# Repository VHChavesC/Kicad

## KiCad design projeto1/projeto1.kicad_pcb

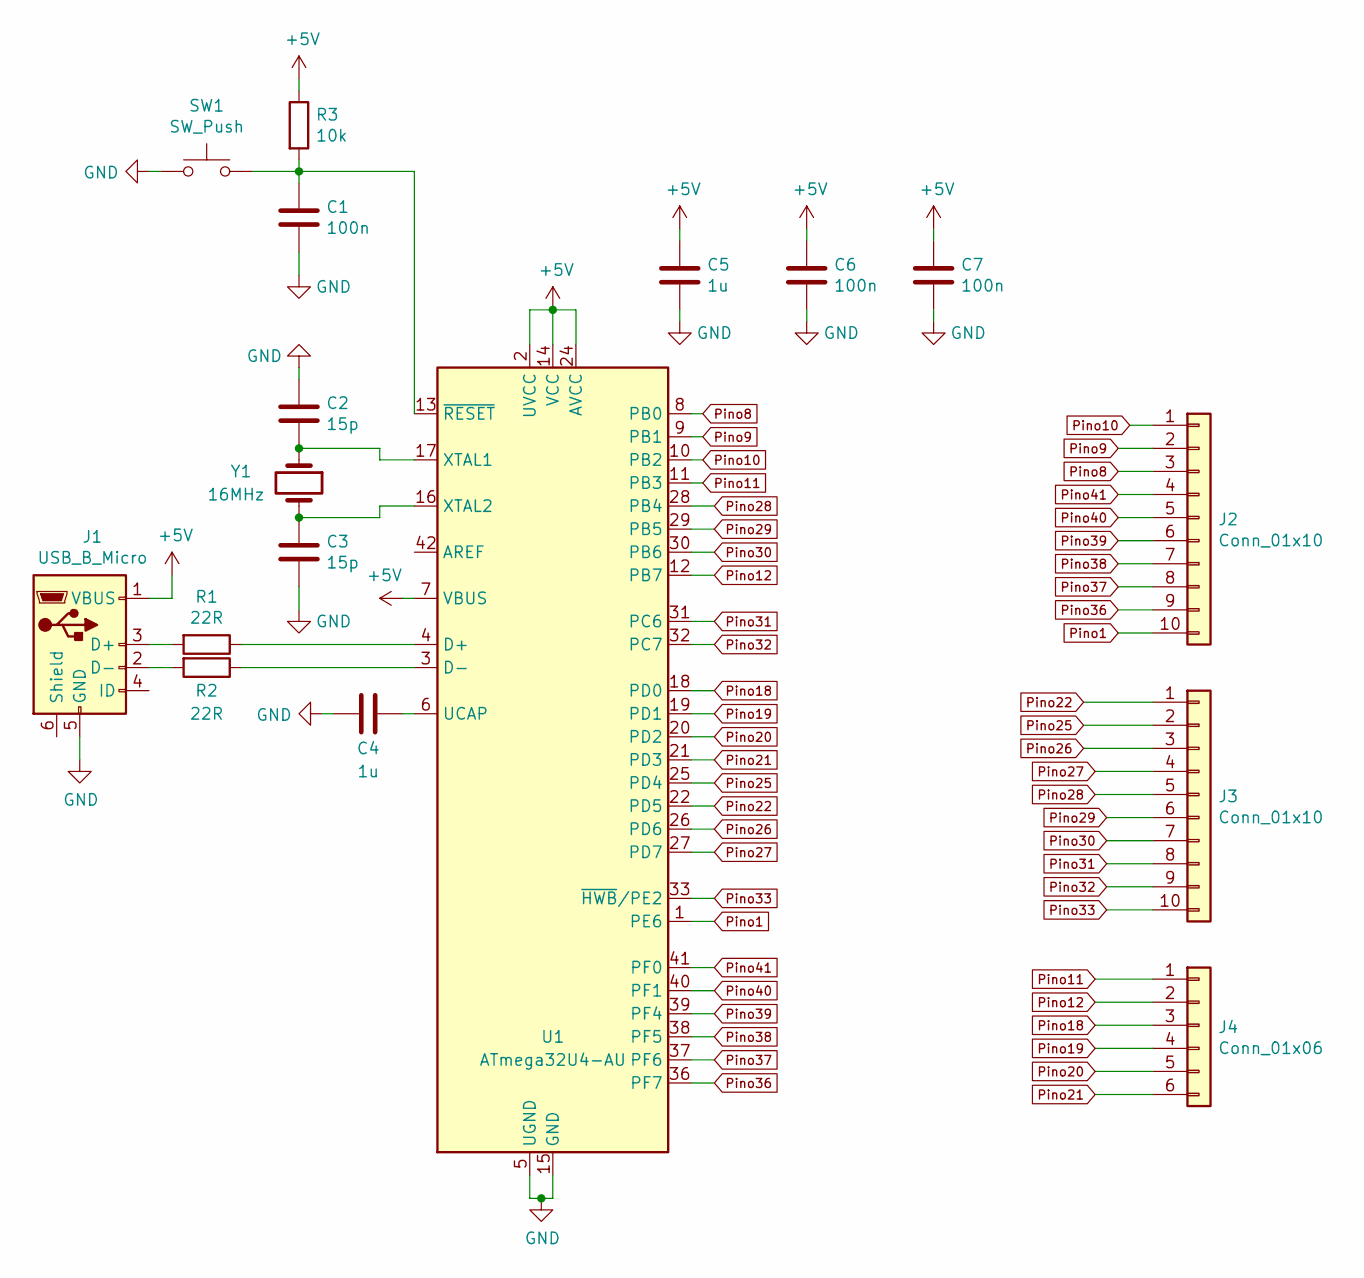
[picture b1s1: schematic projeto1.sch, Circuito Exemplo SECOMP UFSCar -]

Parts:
C1, C6, C7: 100n; C_0805_2012Metric_Pad1.15x1.40mm_HandSolder
C2, C3: 15p; C_0805_2012Metric_Pad1.15x1.40mm_HandSolder
C4, C5: 1u; C_0805_2012Metric_Pad1.15x1.40mm_HandSolder
J1: USB_B_Micro; USB_Mini-B_AdamTech_MUSB-B5-S-VT-TSMT-1_SMD_Vertical
J2, J3: Conn_01x10; PinHeader_1x10_P2.54mm_Vertical
J4: Conn_01x06; PinHeader_1x06_P2.54mm_Vertical
R1, R2: 22R; R_1206_3216Metric_Pad1.42x1.75mm_HandSolder
R3: 10k; R_1206_3216Metric_Pad1.42x1.75mm_HandSolder
SW1: SW_Push; SW_PUSH_6mm
U1: ATmega32U4-AU; TQFP-44_10x10mm_P0.8mm
Y1: 16MHz; Crystal_SMD_5032-2Pin_5.0x3.2mm_HandSoldering

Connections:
+5V: C5.1, C6.1, C7.1, J1.1 (VBUS), R3.1, U1.2 (UVCC), U1.7 (VBUS), U1.14 (VCC), U1.24 (AVCC), U1.34 (VCC), U1.44 (AVCC)
GND: C1.2, C2.1, C3.2, C4.2, C5.2, C6.2, C7.2, J1.5 (GND), SW1.1, U1.5 (UGND), U1.15 (GND), U1.23 (GND), U1.35 (GND), U1.43 (GND)
unnamed: C1.1, R3.2, SW1.2, U1.13 (~RESET)
unnamed: C2.2, U1.17 (XTAL1), Y1.1
unnamed: C3.1, U1.16 (XTAL2), Y1.2
unnamed: C4.1, U1.6 (UCAP)
unnamed: J1.2 (D-), R2.2
unnamed: J1.3 (D+), R1.2
unnamed: R1.1, U1.4 (D+)
unnamed: R2.1, U1.3 (D-)
Pino1: J2.10, U1.1 (PE6)
Pino8: J2.3, U1.8 (PB0)
Pino9: J2.2, U1.9 (PB1)
Pino10: J2.1, U1.10 (PB2)
Pino11: J4.1, U1.11 (PB3)
Pino12: J4.2, U1.12 (PB7)
Pino18: J4.3, U1.18 (PD0)
Pino19: J4.4, U1.19 (PD1)
Pino20: J4.5, U1.20 (PD2)
Pino21: J4.6, U1.21 (PD3)
Pino22: J3.1, U1.22 (PD5)
Pino25: J3.2, U1.25 (PD4)
Pino26: J3.3, U1.26 (PD6)
Pino27: J3.4, U1.27 (PD7)
Pino28: J3.5, U1.28 (PB4)
Pino29: J3.6, U1.29 (PB5)
Pino30: J3.7, U1.30 (PB6)
Pino31: J3.8, U1.31 (PC6)
Pino32: J3.9, U1.32 (PC7)
Pino33: J3.10, U1.33 (~HWB~/PE2)
Pino36: J2.9, U1.36 (PF7)
Pino37: J2.8, U1.37 (PF6)
Pino38: J2.7, U1.38 (PF5)
Pino39: J2.6, U1.39 (PF4)
Pino40: J2.5, U1.40 (PF1)
Pino41: J2.4, U1.41 (PF0)

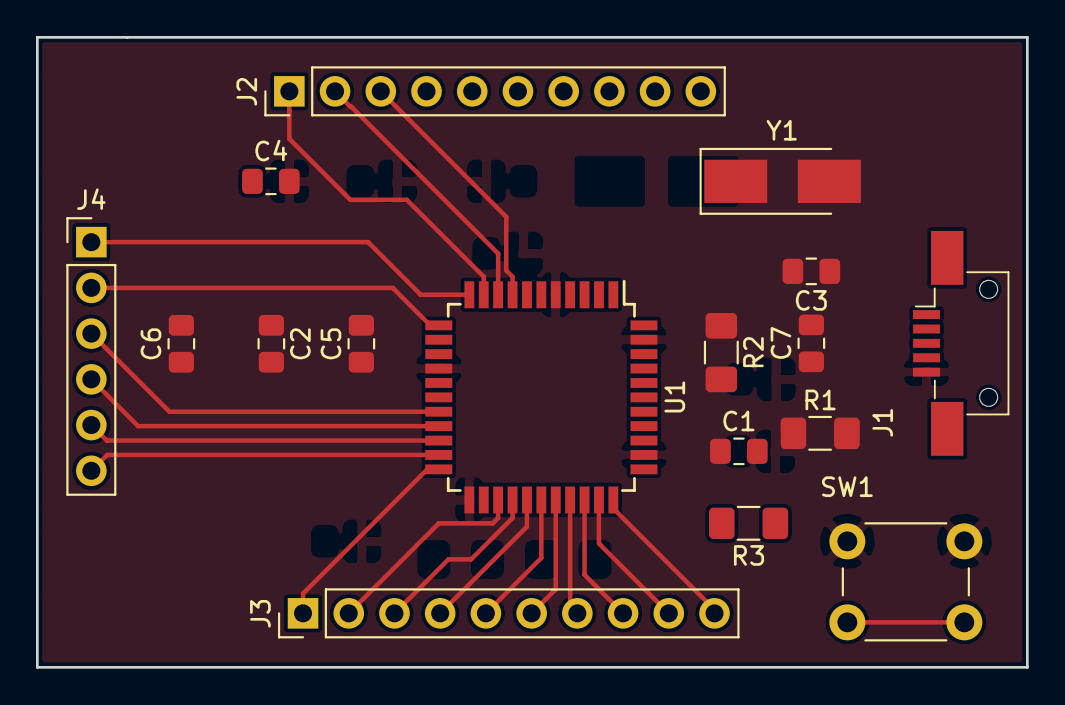
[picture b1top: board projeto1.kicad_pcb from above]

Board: 2 copper layers, 55.0 x 35.0 mm, 17 parts (0 on the bottom side), 36 nets.

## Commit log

2019-09-12 arquivo esquemático com USB
2019-09-12 Crystal, Capacitores de Bypass e UCAP adicionados
2019-09-12 Reset e Pin Headers adicionados
2019-09-12 Identificadores adicionados
2019-09-12 Footprints atribuidas
2019-09-12 Arquivo PDF adicionado
2019-09-12 Processo de alocação dos componentes no PCB iniciado.
2019-09-12 Arquivos para a fabricação gerados
2019-09-12 Correção no Plano do GND
2019-09-12 Adição das anotações relevantes
